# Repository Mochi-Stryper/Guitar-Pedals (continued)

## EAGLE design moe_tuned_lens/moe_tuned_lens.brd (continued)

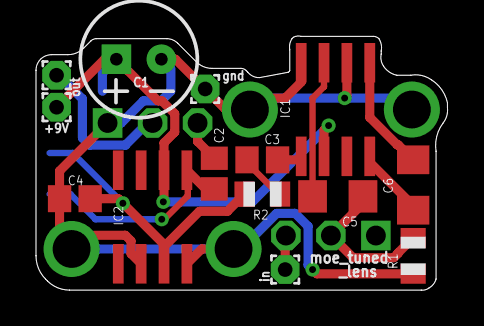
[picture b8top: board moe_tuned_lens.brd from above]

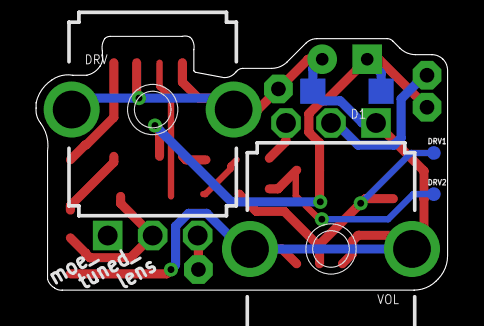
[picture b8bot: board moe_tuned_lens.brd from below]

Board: 2 copper layers, 22.9 x 14.1 mm, 19 parts (5 on the bottom side), 13 nets.
